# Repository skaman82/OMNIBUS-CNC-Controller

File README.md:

# OMNIBUS-CNC-Controller (WORK IN PROGRESS)
CNC Control Project (GRBL and ESTLCAM based). Please dont' sell the boards published here without my consent.

## OMNIBUS ESTLCAM Controller</br>
### FINISHED
</br>
• 8 inputs for sensors and buttons (IN6 is usable if you remoove the LED "L" from the Nano)</br>
• All inputs are isolated with optocouplers</br>
• Inputs 1-3 have selectable voltage (5/12v) so you can connect inductive proximity sensors directly</br>
• VFD outputs (Spindle ON/OFF and RPM control)</br>
• 5V PWM output</br>
• 3 Outputs for relays - the outputs have selectable voltage (5/12v) - OUT3 is automatically enabled on spindle ON</br>
• Feed/Speed override connectors (JST XH 3P)</br>
• Header for bluetooth serial module (HC-05)</br>
• Screw-Terminals for easy connection</br>
• Connector for the DRV-Shield</br>
</br>
## OMNIBUS GRBL 1.1 Controller - also ESTLCAM compatible</br>
### FINISHED
</br>
• Limit-Inputs XYZ have selectable voltage (5/12v) so you can connect inductive proximity sensors directly</br>
• ABORT/HOLD/RESUME/PROBE inputs</br>
• All inputs are isolated with optocouplers</br>
• VFD outputs (Spindle ON/OFF and RPM control)</br>
• 5V PWM Output</br>
• 2 Outputs for relay (SPINDLE_RELAIS / COOLANT) - the outputs have selectable voltage (5/12v) - SPINDLE RELAY is automatically enabled on spindle ON</br>
• Header for bluetooth serial module (HC-05)</br>
• Header for offline controller</br>
• Screw-Terminals for easy connection</br>
• Connector for the DRV-Shield</br>

NOTE: To use the "SPINDLE RELAY" and "VFD RUN" Outputs, please uncomment "define USE_SPINDLE_DIR_AS_ENABLE_PIN" in the GRBL config.h file.
</br>
## OMNIBUS DRV SHIELD (mounts on top the controll PCB with spacers)</br>
### Experimental stage
</br>
• Up to 10A current support (2oz copper PCB required)</br>
• 3-Axis stepper driver support (DRV8825/S109/TMC2100) with stepping config jumpers</br>
• Header for laser module (3p)</br>
• Laser module safety switch - PWM controlled</br>
• Header for an extra 12V 2A BEC to power a laser module (20w max)</br>
• 12V fan header</br>
• 12V Power supply for the OMNIBUS controller (so you don't need an extra 12v PSU for the controll board)</br>
• Screw-Terminals for easy connection</br>

NOTE: If powerting the OMNIBUS Controller with the DRV Shield, use a heatsink on the 12V LDO and provide good airflow - the LDO is getting hot and will
shut down if thermal protection kicks in.

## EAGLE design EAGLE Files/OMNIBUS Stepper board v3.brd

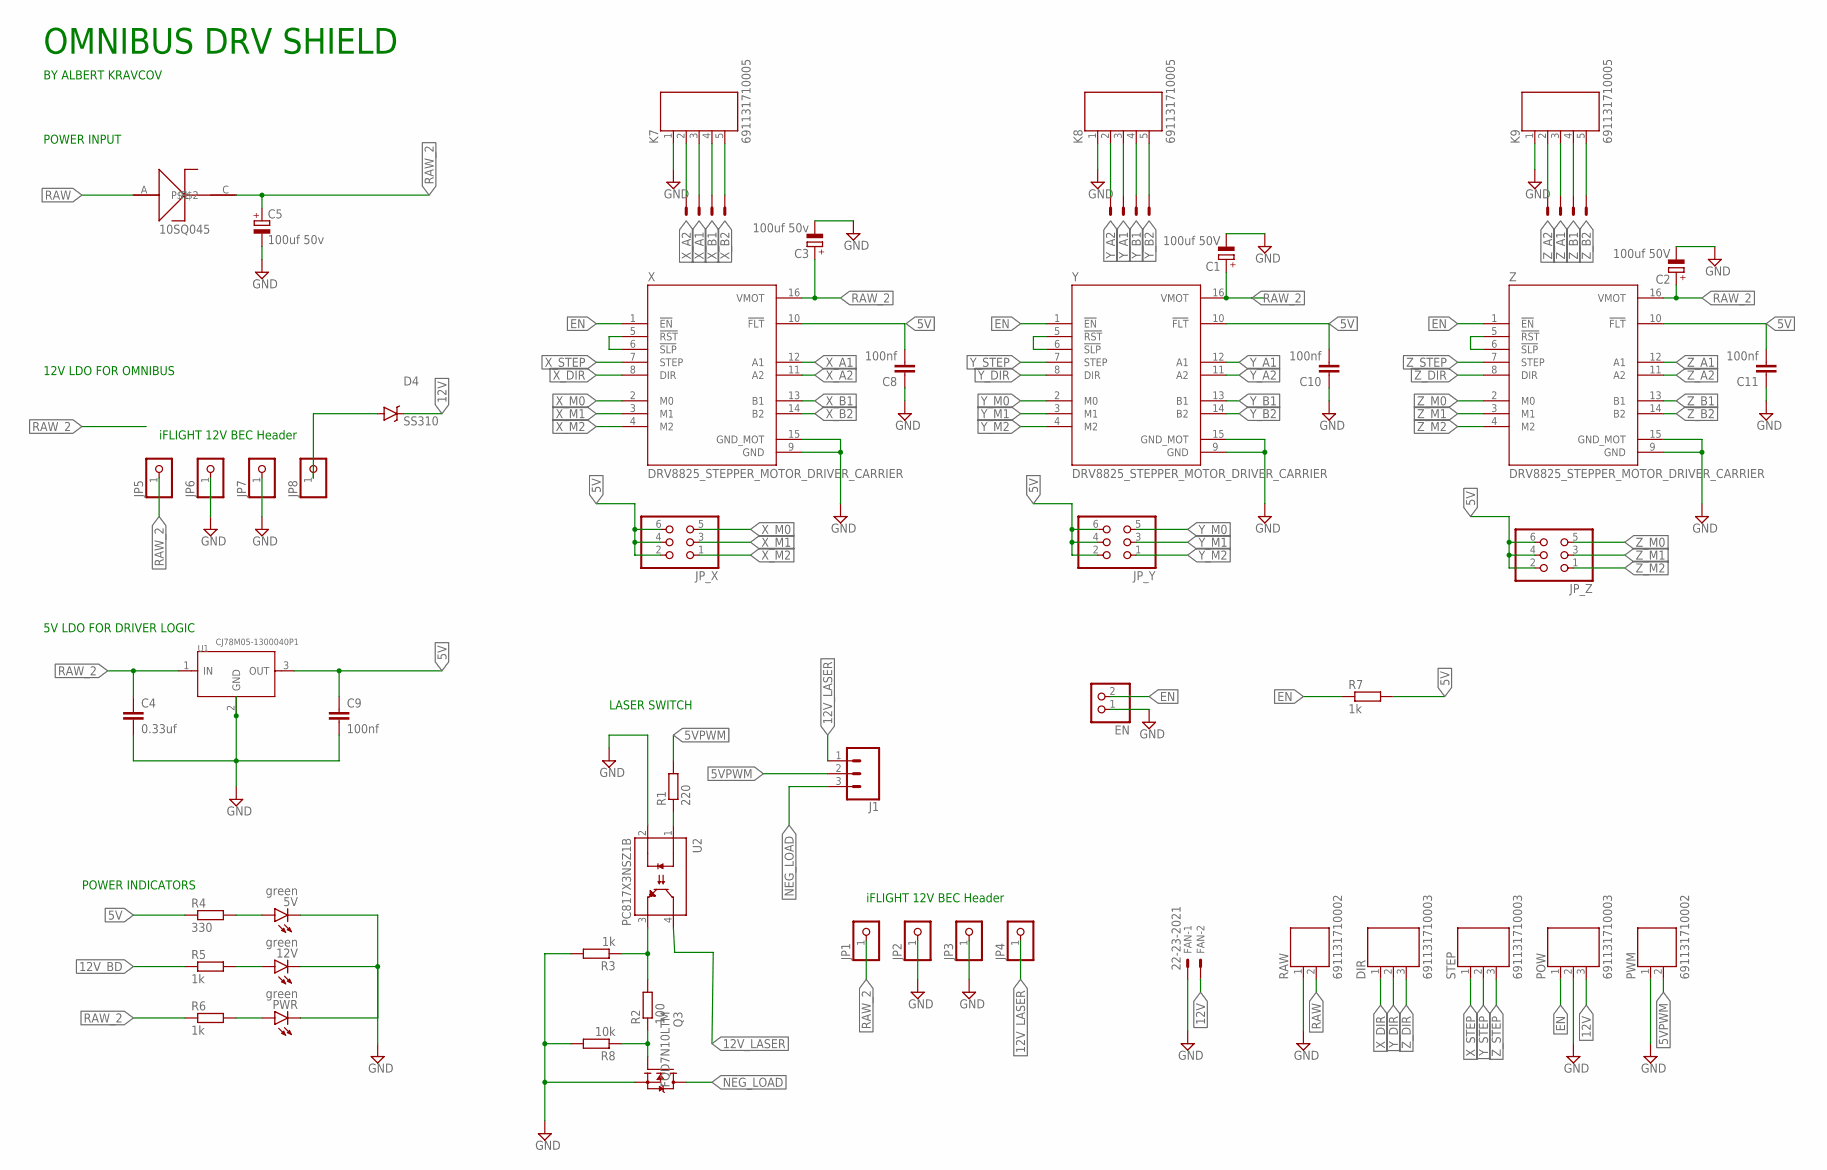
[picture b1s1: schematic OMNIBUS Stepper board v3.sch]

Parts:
5V, 12V: green; CHIPLED_0805
C1, C2: 100uf 50V; E5-6
C3: 100uf 50v; E5-6
C4: 0.33uf; C1206
C5: 100uf 50v; E5-8,5
C8, C10, C11: 100nf; C0805
C9: 100nf; C1206
D1: 10SQ045; DIOAD885W125L910D885
D4: SS310; DO-214AC
DIR: 691131710003
EN: PINHD-1X2; 1X02
FAN: 22-23-2021
J1: CONN_03; 1X03
JP1, JP2, JP3, JP4, JP5, JP6, JP7, JP8: PINHD-1X1; 1X01
JP_X: PINHD-2X3; 2X03
JP_Y: PINHD-2X3; 2X03
JP_Z: PINHD-2X3; 2X03
K7, K8, K9: 691131710005
POW: 691131710003
PWM: 691131710002
PWR: green; CHIPLED_0805
Q3: FQD7N10LTM; TO-252
R1: 220; R0805
R2: 100; R0805
R3, R5, R7: 1k; R0805
R4: 330; R0805
R6: 1k; R1206
R8: 10k; R0805
RAW: 691131710002
STEP: 691131710003
U1: CJ78M05-1300040P1; TO252
U2: PC817X3NSZ1B; DIP762W50P254L495H455Q4
X: DRV8825_STEPPER_MOTOR_DRIVER_CARRIER; IC_DRV8825_STEPPER_MOTOR_DRIVER_CARRIER
X_MOTOR: 22-23-2041
Y: DRV8825_STEPPER_MOTOR_DRIVER_CARRIER; IC_DRV8825_STEPPER_MOTOR_DRIVER_CARRIER
Y_MOTOR: 22-23-2041
Z: DRV8825_STEPPER_MOTOR_DRIVER_CARRIER; IC_DRV8825_STEPPER_MOTOR_DRIVER_CARRIER
Z_MOTOR: 22-23-2041

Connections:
5V: C8.2, C9.1, C10.2, C11.2, JP_X.2, JP_X.4, JP_X.6, JP_Y.2, JP_Y.4, JP_Y.6, JP_Z.2, JP_Z.4, JP_Z.6, R4.1, R7.2, U1.3 (OUT), X.10 (!FLT), Y.10 (!FLT), Z.10 (!FLT)
5VPWM: J1.2, PWM.2, R1.2
12V: D4.C, FAN.2, POW.3
12V_BD: D4.A, JP8.1, R5.1
12V_LASER: J1.1, JP4.1, U2.4 (COLLECTOR)
EN: EN.2, POW.1, R7.1, X.1 (!EN), Y.1 (!EN), Z.1 (!EN)
GND: 5V.C, 12V.C, C1.-, C2.-, C3.-, C4.2, C5.-, C8.1, C9.2, C10.1, C11.1, EN.1, FAN.1, JP2.1, JP3.1, JP6.1, JP7.1, K7.1, K8.1, K9.1, POW.2, PWM.1, PWR.C, Q3.3 (S), R3.2, R8.2, RAW.1, U1.2 (GND), U2.2 (CATHODE), X.9 (GND), X.15 (GND_MOT), Y.9 (GND), Y.15 (GND_MOT), Z.9 (GND), Z.15 (GND_MOT)
unnamed: Q3.1 (G), R2.1, R8.1
unnamed: 5V.A, R4.2
unnamed: R1.1, U2.1 (ANODE)
unnamed: R2.2, R3.1, U2.3 (EMITTER)
unnamed: 12V.A, R5.2
unnamed: PWR.A, R6.2
NC: Z.5 (!RST), Z.6 (!SLP)
NC2: Y.5 (!RST), Y.6 (!SLP)
NC3: X.5 (!RST), X.6 (!SLP)
NEG_LOAD: J1.3, Q3.T (D)
RAW: D1.A, RAW.2
RAW_2: C1.+, C2.+, C3.+, C4.1, C5.+, D1.C, JP1.1, JP5.1, R6.1, U1.1 (IN), X.16 (VMOT), Y.16 (VMOT), Z.16 (VMOT)
X_A1: K7.3, X.12 (A1), X_MOTOR.3
X_A2: K7.2, X.11 (A2), X_MOTOR.4
X_B1: K7.4, X.13 (B1), X_MOTOR.2
X_B2: K7.5, X.14 (B2), X_MOTOR.1
X_DIR: DIR.1, X.8 (DIR)
X_M0: JP_X.5, X.2 (M0)
X_M1: JP_X.3, X.3 (M1)
X_M2: JP_X.1, X.4 (M2)
X_STEP: STEP.1, X.7 (STEP)
Y_A1: K8.3, Y.12 (A1), Y_MOTOR.3
Y_A2: K8.2, Y.11 (A2), Y_MOTOR.4
Y_B1: K8.4, Y.13 (B1), Y_MOTOR.2
Y_B2: K8.5, Y.14 (B2), Y_MOTOR.1
Y_DIR: DIR.2, Y.8 (DIR)
Y_M0: JP_Y.5, Y.2 (M0)
Y_M1: JP_Y.3, Y.3 (M1)
Y_M2: JP_Y.1, Y.4 (M2)
Y_STEP: STEP.2, Y.7 (STEP)
Z_A1: K9.3, Z.12 (A1), Z_MOTOR.3
Z_A2: K9.2, Z.11 (A2), Z_MOTOR.4
Z_B1: K9.4, Z.13 (B1), Z_MOTOR.2
Z_B2: K9.5, Z.14 (B2), Z_MOTOR.1
Z_DIR: DIR.3, Z.8 (DIR)
Z_M0: JP_Z.5, Z.2 (M0)
Z_M1: JP_Z.3, Z.3 (M1)
Z_M2: JP_Z.1, Z.4 (M2)
Z_STEP: STEP.3, Z.7 (STEP)

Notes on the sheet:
LASER SWITCH
POWER INPUT
5V LDO FOR DRIVER LOGIC
12V LDO FOR OMNIBUS
POWER INDICATORS
iFLIGHT 12V BEC Header
OMNIBUS DRV SHIELD
BY ALBERT KRAVCOV
10SQ045

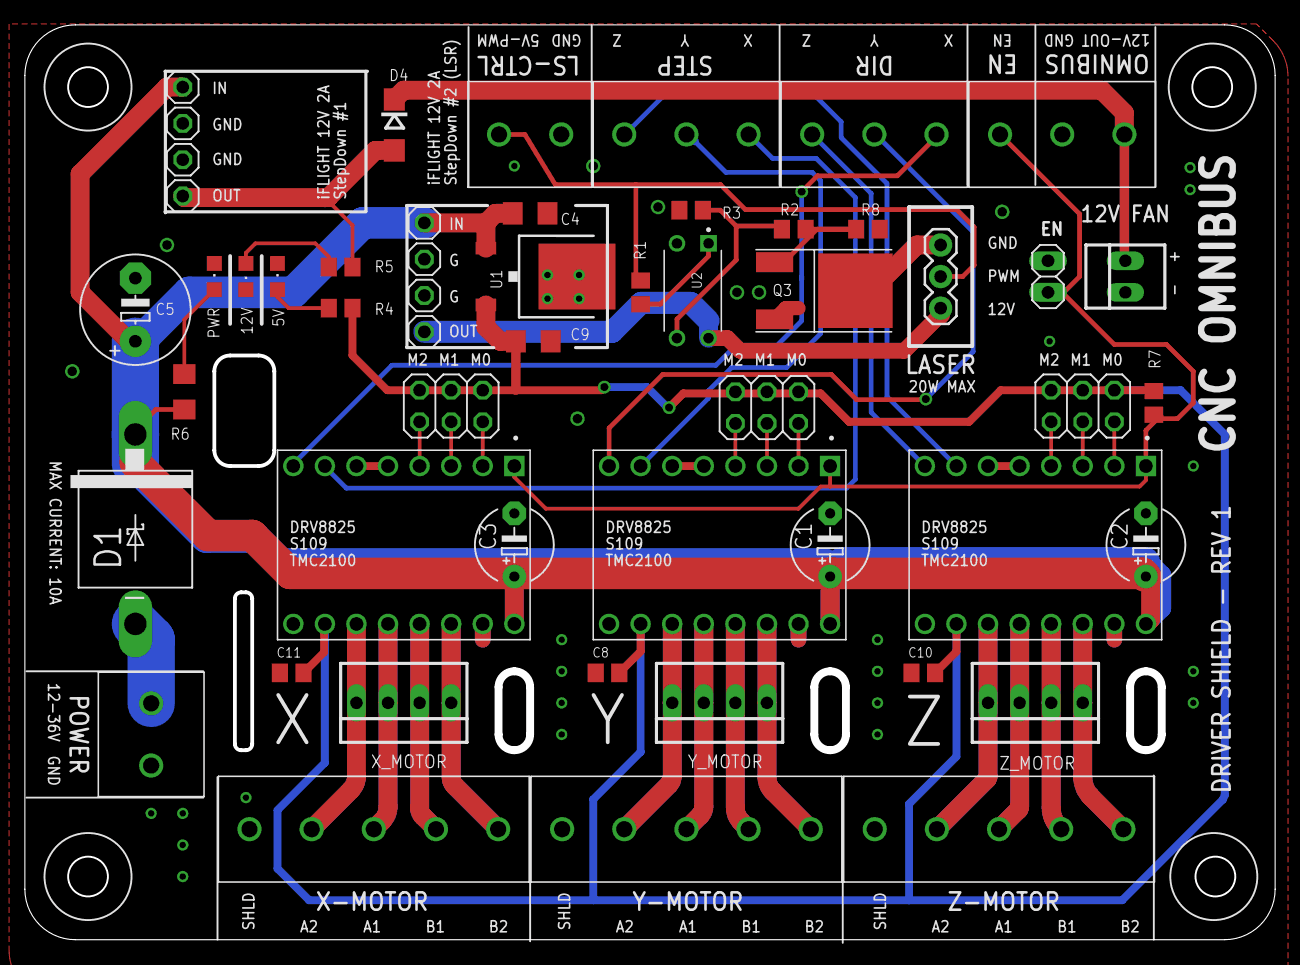
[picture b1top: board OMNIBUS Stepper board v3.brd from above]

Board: 2 copper layers, 99.9 x 72.9 mm, 53 parts (0 on the bottom side), 46 nets.

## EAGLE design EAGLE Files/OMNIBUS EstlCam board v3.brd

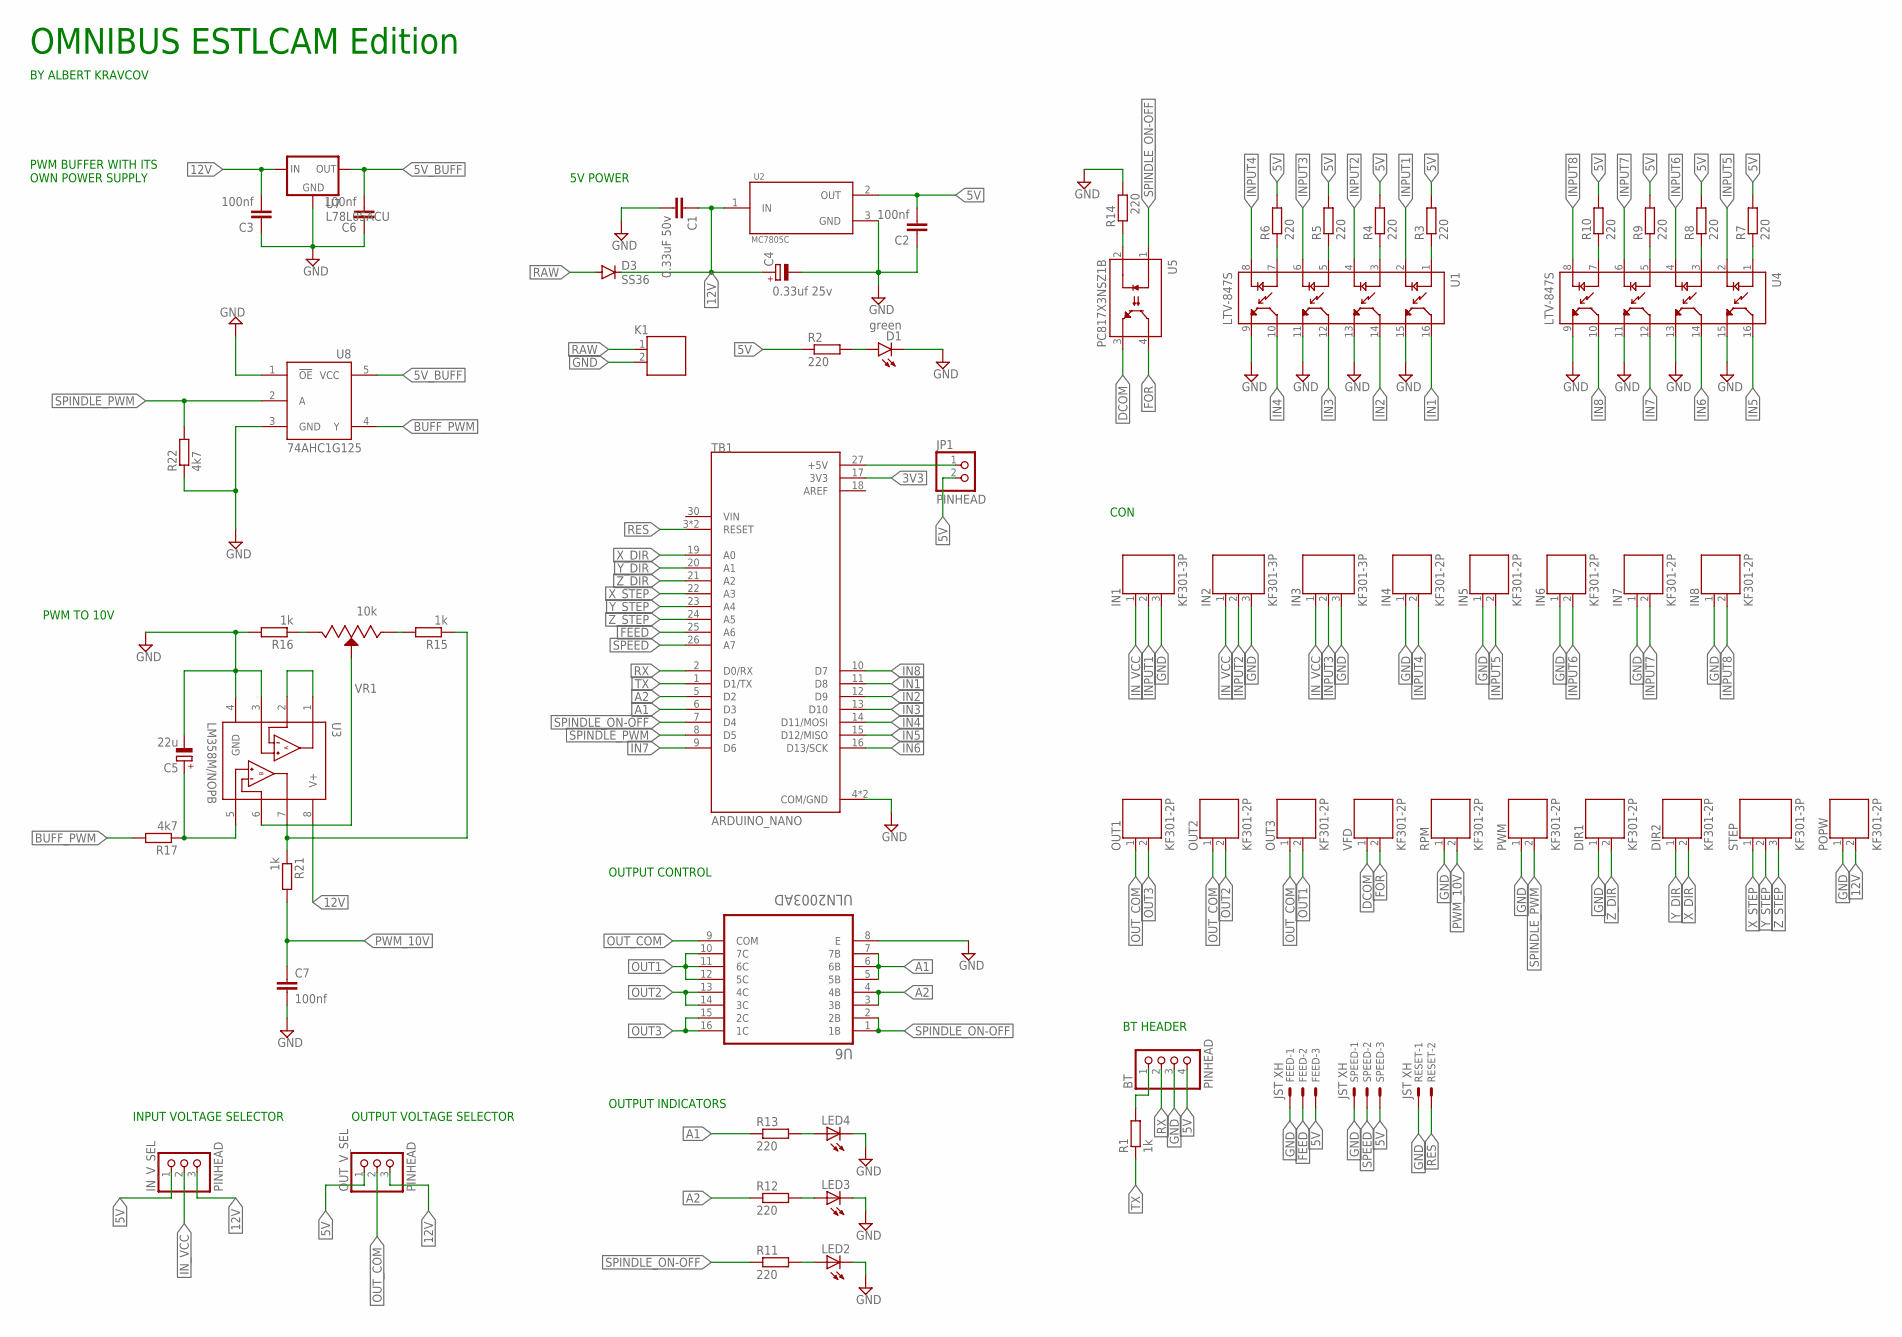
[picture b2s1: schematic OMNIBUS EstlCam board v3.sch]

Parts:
BT: PINHEAD; 1X04
C1: 0.33uF 50v; C1206
C2, C3, C6, C7: 100nf; C0805
C4: 0.33uf 25v; E2-5
C5: 22u; E2-5
D1: green; CHIPLED_0805
D3: SS36; SMB
DIR1, DIR2: KF301-2P; 691131710002
FEED: JST XH; 22-23-2031
IN1, IN2, IN3: KF301-3P; 691131710003
IN4, IN5, IN6, IN7, IN8: KF301-2P; 691131710002
IN_V_SEL: PINHEAD; 1X03
JP1: PINHEAD; 1X02
K1: 691131710002
LED2, LED3, LED4: LED_ESML0603; LED_SML0603
OUT1, OUT2, OUT3: KF301-2P; 691131710002
OUT_V_SEL: PINHEAD; 1X03
POPW: KF301-2P; 691131710002
PWM: KF301-2P; 691131710002
R1, R15, R16, R21: 1k; R0805
R2, R3, R4, R5, R6, R7, R8, R9, R10, R14: 220; R0805
R11, R12, R13: 220; R0603
R17: 4k7; R0603
R22: 4k7; R0805
RESET: JST XH; 22-23-2021
RPM: KF301-2P; 691131710002
SPEED: JST XH; 22-23-2031
STEP: KF301-3P; 691131710003
TB1: ARDUINO_NANO; SHIELD_ARDUINO_NANO
U1, U4: LTV-847S; SOIC254P1016X460-16N
U2: MC7805C; TO254P1515X470-3N
U3: LM358M/NOPB; SOIC127P599X175-8N
U5: PC817X3NSZ1B; DIP762W50P254L495H455Q4
U6: ULN2003AD; SOIC127P600X175-16N
U7: L78L05ACU; SOT89
U8: 74AHC1G125; SOT23-5L
VFD: KF301-2P; 691131710002
VR1: 10k; TRIM_3296W-1-502

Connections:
3V3: TB1.17 (3V3)
5V: BT.4, C2.2, FEED.3, IN_V_SEL.1, JP1.2, OUT_V_SEL.1, R2.1, R3.2, R4.2, R5.2, R6.2, R7.2, R8.2, R9.2, R10.2, SPEED.3, U2.2 (OUT)
5V_BUFF: C6.2, U7.1 (OUT), U8.5 (VCC)
12V: C1.1, C3.2, C4.+, D3.C, IN_V_SEL.3, OUT_V_SEL.3, POPW.2, U2.1 (IN), U3.8 (V+), U7.3 (IN)
A1: R13.1, TB1.6 (D3), U6.5 (5B), U6.6 (6B), U6.7 (7B)
A2: R12.1, TB1.5 (D2), U6.3 (3B), U6.4 (4B)
ARDU5V: JP1.1, TB1.27 (+5V)
AREF: TB1.18 (AREF)
BUFF_PWM: R17.2, U8.4 (Y)
D: R15.1, R21.1, U3.7 (OUTB)
DCOM: U5.3 (EMITTER), VFD.1
FEED: FEED.2, TB1.25 (A6)
FOR: U5.4 (COLLECTOR), VFD.2
GND: BT.3, C1.2, C2.1, C3.1, C4.-, C5.-, C6.1, C7.2, D1.C, DIR1.1, FEED.1, IN1.3, IN2.3, IN3.3, IN4.1, IN5.1, IN6.1, IN7.1, IN8.1, K1.2, LED2.C, LED3.C, LED4.C, POPW.1, PWM.1, R14.2, R16.2, R22.1, RESET.1, RPM.1, SPEED.1, TB1.4 (COM/GND), TB1.29 (COM/GND), U1.9 (ET3), U1.11 (ET2), U1.13 (ET1), U1.15 (ET), U2.3 (GND), U3.3 (+INA), U3.4 (GND), U4.9 (ET3), U4.11 (ET2), U4.13 (ET1), U4.15 (ET), U6.8 (E), U7.2 (GND), U8.1 (!OE), U8.3 (GND)
IN1: TB1.11 (D8), U1.16 (CT)
IN2: TB1.12 (D9), U1.14 (CT1)
IN3: TB1.13 (D10), U1.12 (CT2)
IN4: TB1.14 (D11/MOSI), U1.10 (CT3)
IN5: TB1.15 (D12/MISO), U4.16 (CT)
IN6: TB1.16 (D13/SCK), U4.14 (CT1)
IN7: TB1.9 (D6), U4.12 (CT2)
IN8: TB1.10 (D7), U4.10 (CT3)
INPUT1: IN1.2, U1.2 (C)
INPUT2: IN2.2, U1.4 (C1)
INPUT3: IN3.2, U1.6 (C2)
INPUT4: IN4.2, U1.8 (C3)
INPUT5: IN5.2, U4.2 (C)
INPUT6: IN6.2, U4.4 (C1)
INPUT7: IN7.2, U4.6 (C2)
INPUT8: IN8.2, U4.8 (C3)
IN_VCC: IN1.1, IN2.1, IN3.1, IN_V_SEL.2
unnamed: D1.A, R2.2
unnamed: R4.1, U1.3 (A1)
unnamed: R5.1, U1.5 (A2)
unnamed: R6.1, U1.7 (A3)
unnamed: R3.1, U1.1 (A)
unnamed: R7.1, U4.1 (A)
unnamed: R8.1, U4.3 (A1)
unnamed: R9.1, U4.5 (A2)
unnamed: R10.1, U4.7 (A3)
unnamed: LED3.A, R12.2
unnamed: LED2.A, R11.2
unnamed: LED4.A, R13.2
unnamed: R14.1, U5.2 (CATHODE)
unnamed: U3.6 (-INB), VR1.2 (WIPER)
unnamed: R15.2, VR1.1 (CCW)
unnamed: R16.1, VR1.3 (CW)
unnamed: C5.+, R17.1, U3.5 (+INB)
unnamed: U3.1 (OUTA), U3.2 (-INA)
unnamed: BT.1, R1.2
OUT1: OUT3.2, U6.10 (7C), U6.11 (6C), U6.12 (5C)
OUT2: OUT2.2, U6.13 (4C), U6.14 (3C)
OUT3: OUT1.2, U6.15 (2C), U6.16 (1C)
OUT_COM: OUT1.1, OUT2.1, OUT3.1, OUT_V_SEL.2, U6.9 (COM)
PWM_10V: C7.1, R21.2, RPM.2
RAW: D3.A, K1.1
RES: RESET.2, TB1.3 (RESET), TB1.28 (RESET)
RX: BT.2, TB1.2 (D0/RX)
SPEED: SPEED.2, TB1.26 (A7)
SPINDLE_ON-OFF: R11.1, TB1.7 (D4), U5.1 (ANODE), U6.1 (1B), U6.2 (2B)
SPINDLE_PWM: PWM.2, R22.2, TB1.8 (D5), U8.2 (A)
TX: R1.1, TB1.1 (D1/TX)
X_DIR: DIR2.2, TB1.19 (A0)
X_STEP: STEP.1, TB1.22 (A3)
Y_DIR: DIR2.1, TB1.20 (A1)
Y_STEP: STEP.2, TB1.23 (A4)
Z_DIR: DIR1.2, TB1.21 (A2)
Z_STEP: STEP.3, TB1.24 (A5)

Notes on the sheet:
PWM BUFFER WITH ITS OWN POWER SUPPLY
OUTPUT VOLTAGE SELECTOR
PWM TO 10V
INPUT VOLTAGE SELECTOR
OUTPUT INDICATORS
OUTPUT CONTROL
CON
5V POWER
BT HEADER
OMNIBUS ESTLCAM Edition
BY ALBERT KRAVCOV

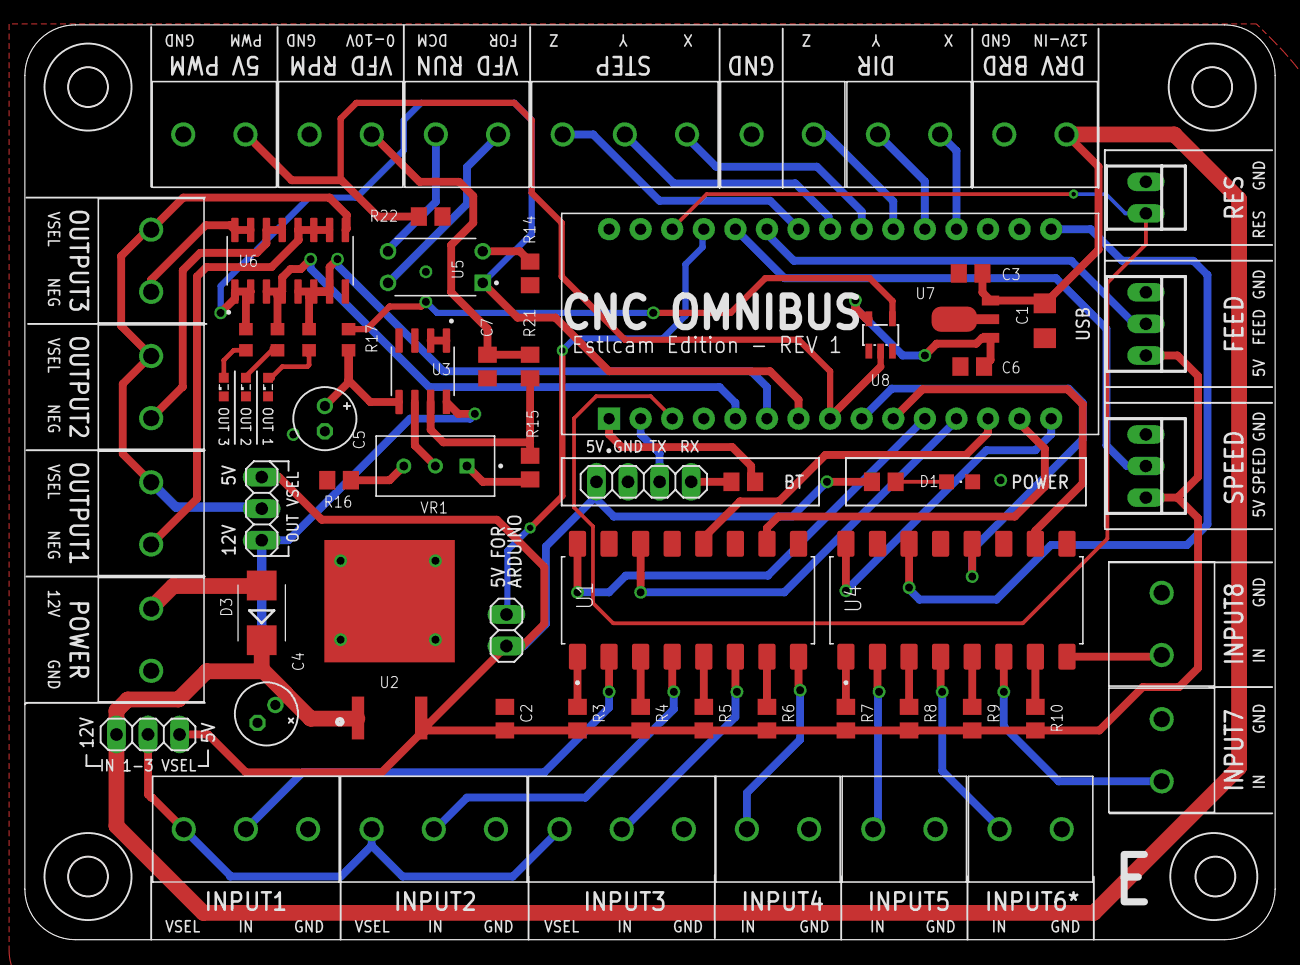
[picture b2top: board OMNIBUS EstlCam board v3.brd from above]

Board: 2 copper layers, 100.4 x 73.4 mm, 67 parts (0 on the bottom side), 66 nets.

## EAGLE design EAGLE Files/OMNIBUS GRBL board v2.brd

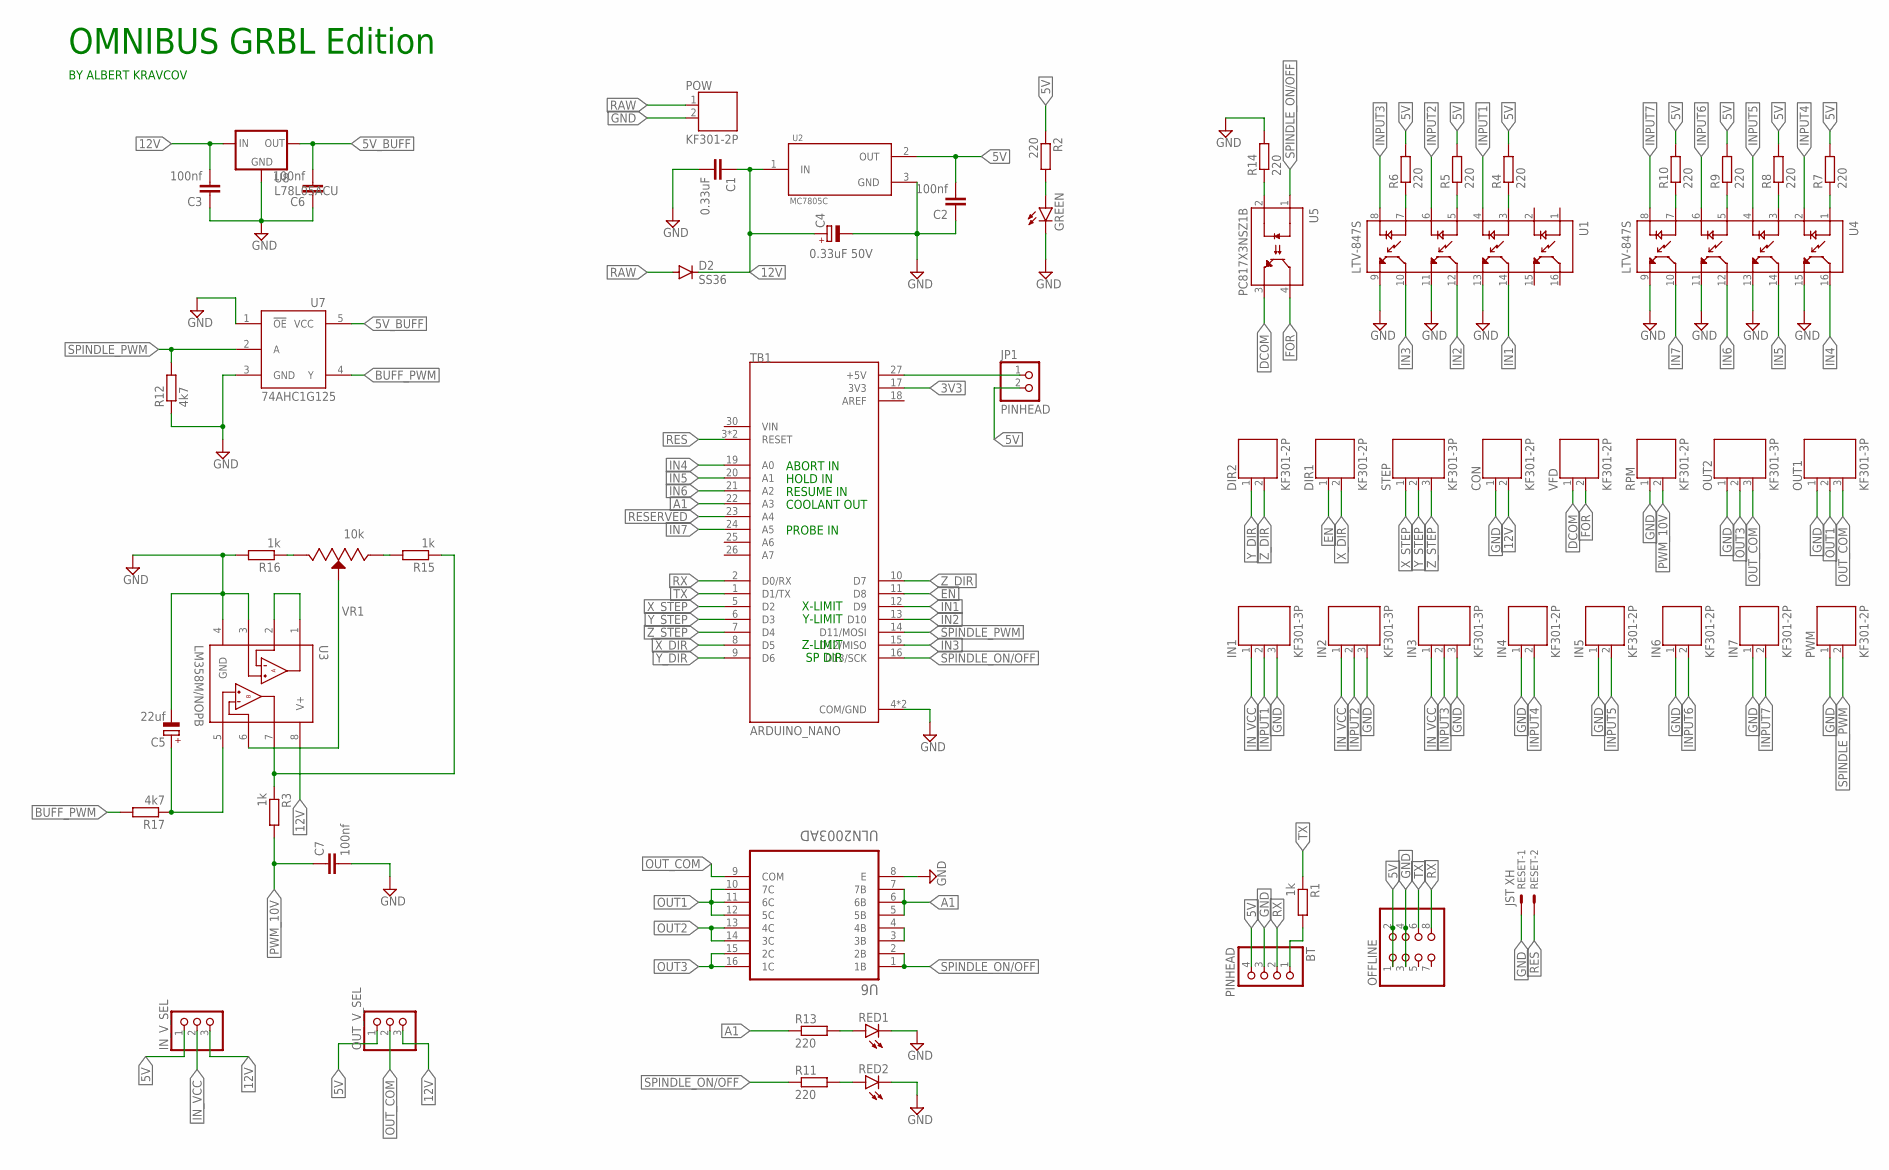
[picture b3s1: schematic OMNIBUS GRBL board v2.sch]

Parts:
BT: PINHEAD; 1X04
C1: 0.33uF; C1206K
C2: 100nf; C0805K
C3, C6, C7: 100nf; C0805
C4: 0.33uF 50V; E2-5
C5: 22uf; E2-5
CON: KF301-2P; 691131710002
D2: SS36; SMB
DIR1, DIR2: KF301-2P; 691131710002
GREEN: LEDCHIPLED_0805; CHIPLED_0805
IN1, IN2, IN3: KF301-3P; 691131710003
IN4, IN5, IN6, IN7: KF301-2P; 691131710002
IN_V_SEL: PINHD-1X3; 1X03
JP1: PINHEAD; 1X02
OFFLINE: PINHD-2X4; 2X04
OUT1, OUT2: KF301-3P; 691131710003
OUT_V_SEL: PINHD-1X3; 1X03
POW: KF301-2P; 691131710002
PWM: KF301-2P; 691131710002
R1, R3, R15, R16: 1k; R0805
R2, R11, R13: 220; R0603
R4, R5, R6, R7, R8, R9, R10, R14: 220; R0805
R12, R17: 4k7; R0805
RED1, RED2: LEDCHIPLED_0805; CHIPLED_0805
RESET: JST XH; 22-23-2021
RPM: KF301-2P; 691131710002
STEP: KF301-3P; 691131710003
TB1: ARDUINO_NANO; SHIELD_ARDUINO_NANO
U1, U4: LTV-847S; SOIC254P1016X460-16N
U2: MC7805C; TO254P1515X470-3N
U3: LM358M/NOPB; SOIC127P599X175-8N
U5: PC817X3NSZ1B; DIP762W50P254L495H455Q4
U6: ULN2003AD; SOIC127P600X175-16N
U7: 74AHC1G125; SOT23-5L
U8: L78L05ACU; SOT89
VFD: KF301-2P; 691131710002
VR1: 10k; TRIM_3296W-1-502

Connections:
3V3: TB1.17 (3V3)
5V: BT.4, C2.2, IN_V_SEL.1, JP1.2, OFFLINE.1, OFFLINE.2, OUT_V_SEL.1, R2.1, R4.2, R5.2, R6.2, R7.2, R8.2, R9.2, R10.2, U2.2 (OUT)
5V_BUFF: C6.2, U7.5 (VCC), U8.1 (OUT)
12V: C1.1, C3.2, C4.+, CON.2, D2.C, IN_V_SEL.3, OUT_V_SEL.3, U2.1 (IN), U3.8 (V+), U8.3 (IN)
A1: R13.1, TB1.22 (A3), U6.5 (5B), U6.6 (6B), U6.7 (7B)
A2: U6.3 (3B), U6.4 (4B)
ARDUPWR: JP1.1, TB1.27 (+5V)
AREF: TB1.18 (AREF)
BUFF_PWM: R17.2, U7.4 (Y)
DCOM: U5.3 (EMITTER), VFD.1
EN: DIR1.1, TB1.11 (D8)
FOR: U5.4 (COLLECTOR), VFD.2
GND: BT.3, C1.2, C2.1, C3.1, C4.-, C5.-, C6.1, C7.2, CON.1, GREEN.C, IN1.3, IN2.3, IN3.3, IN4.1, IN5.1, IN6.1, IN7.1, OFFLINE.3, OFFLINE.4, OUT1.1, OUT2.1, POW.2, PWM.1, R12.1, R14.2, R16.2, RED1.C, RED2.C, RESET.1, RPM.1, TB1.4 (COM/GND), TB1.29 (COM/GND), U1.9 (ET3), U1.11 (ET2), U1.13 (ET1), U2.3 (GND), U3.3 (+INA), U3.4 (GND), U4.9 (ET3), U4.11 (ET2), U4.13 (ET1), U4.15 (ET), U6.8 (E), U7.1 (!OE), U7.3 (GND), U8.2 (GND)
IN1: TB1.12 (D9), U1.14 (CT1)
IN2: TB1.13 (D10), U1.12 (CT2)
IN3: TB1.15 (D12/MISO), U1.10 (CT3)
IN4: TB1.19 (A0), U4.16 (CT)
IN5: TB1.20 (A1), U4.14 (CT1)
IN6: TB1.21 (A2), U4.12 (CT2)
IN7: TB1.24 (A5), U4.10 (CT3)
INPUT1: IN1.2, U1.4 (C1)
INPUT2: IN2.2, U1.6 (C2)
INPUT3: IN3.2, U1.8 (C3)
INPUT4: IN4.2, U4.2 (C)
INPUT5: IN5.2, U4.4 (C1)
INPUT6: IN6.2, U4.6 (C2)
INPUT7: IN7.2, U4.8 (C3)
IN_VCC: IN1.1, IN2.1, IN3.1, IN_V_SEL.2
unnamed: GREEN.A, R2.2
unnamed: R4.1, U1.3 (A1)
unnamed: R5.1, U1.5 (A2)
unnamed: R6.1, U1.7 (A3)
unnamed: R7.1, U4.1 (A)
unnamed: R8.1, U4.3 (A1)
unnamed: R9.1, U4.5 (A2)
unnamed: R10.1, U4.7 (A3)
unnamed: R11.2, RED2.A
unnamed: R13.2, RED1.A
unnamed: R14.1, U5.2 (CATHODE)
unnamed: U3.6 (-INB), VR1.2 (WIPER)
unnamed: R15.2, VR1.1 (CCW)
unnamed: R16.1, VR1.3 (CW)
unnamed: C5.+, R17.1, U3.5 (+INB)
unnamed: U3.1 (OUTA), U3.2 (-INA)
unnamed: BT.1, R1.2
OUT1: OUT1.2, U6.10 (7C), U6.11 (6C), U6.12 (5C)
OUT2: U6.13 (4C), U6.14 (3C)
OUT3: OUT2.2, U6.15 (2C), U6.16 (1C)
OUT_COM: OUT1.3, OUT2.3, OUT_V_SEL.2, U6.9 (COM)
PWM_10V: C7.1, R3.1, R3.2, R15.1, RPM.2, U3.7 (OUTB)
RAW: D2.A, POW.1
RES: RESET.2, TB1.3 (RESET), TB1.28 (RESET)
RESERVED: TB1.23 (A4)
RX: BT.2, OFFLINE.8, TB1.2 (D0/RX)
SPINDLE_ON/OFF: R11.1, TB1.16 (D13/SCK), U5.1 (ANODE), U6.1 (1B), U6.2 (2B)
SPINDLE_PWM: PWM.2, R12.2, TB1.14 (D11/MOSI), U7.2 (A)
TX: OFFLINE.6, R1.1, TB1.1 (D1/TX)
X_DIR: DIR1.2, TB1.8 (D5)
X_STEP: STEP.1, TB1.5 (D2)
Y_DIR: DIR2.1, TB1.9 (D6)
Y_STEP: STEP.2, TB1.6 (D3)
Z_DIR: DIR2.2, TB1.10 (D7)
Z_STEP: STEP.3, TB1.7 (D4)

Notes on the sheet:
SP DIR
ABORT IN
HOLD IN
RESUME IN
COOLANT OUT
PROBE IN
Z-LIMIT
Y-LIMIT
X-LIMIT
OMNIBUS GRBL Edition
BY ALBERT KRAVCOV

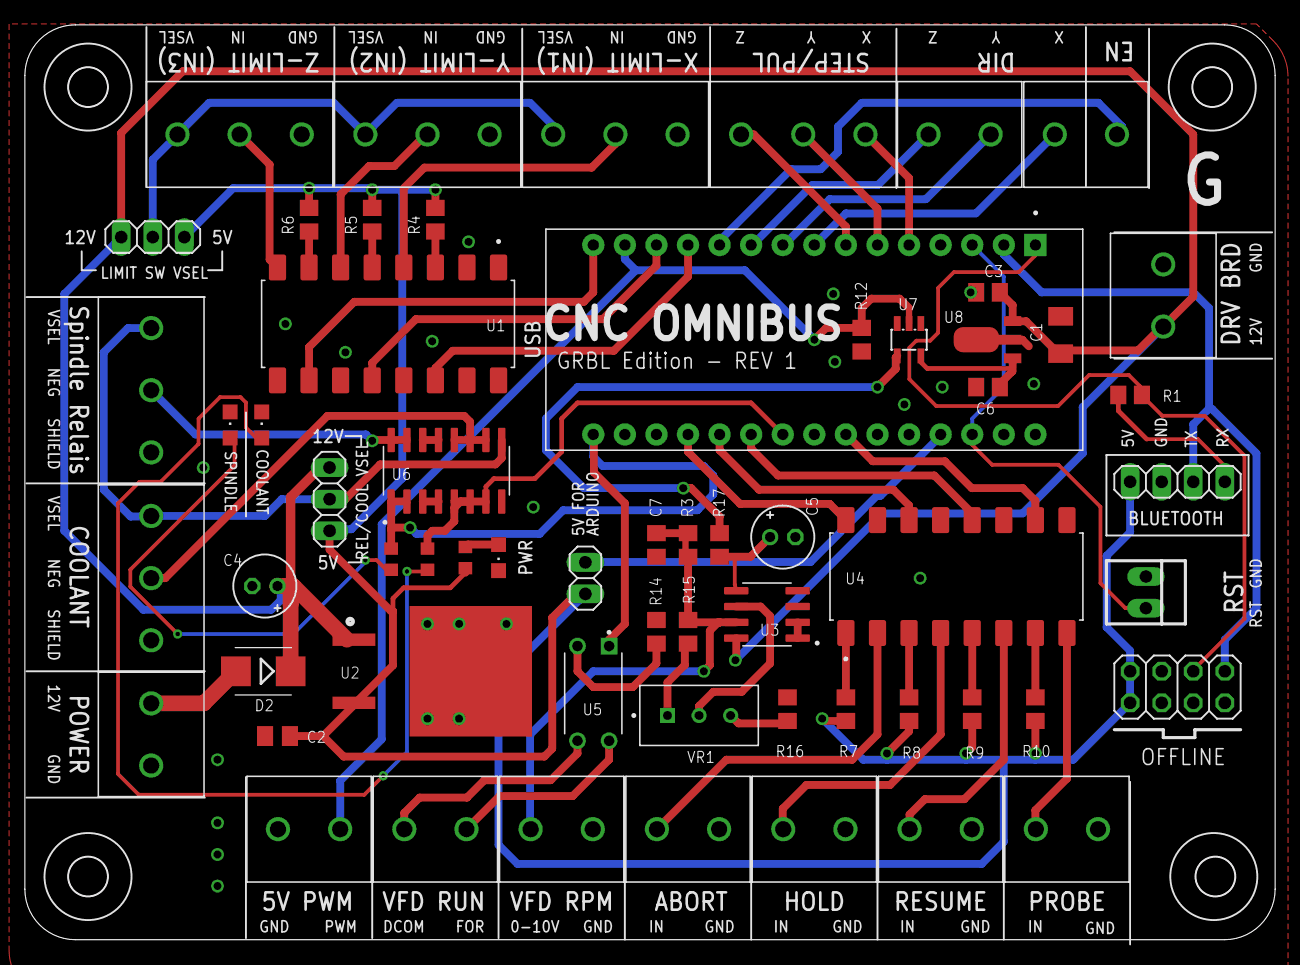
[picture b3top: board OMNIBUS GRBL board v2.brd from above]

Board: 2 copper layers, 100.4 x 73.4 mm, 61 parts (0 on the bottom side), 60 nets.

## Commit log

2021-05-05 Initial File Upload
2021-05-05 Reorder
2021-05-05 Renaming Files
2021-05-05 Extra files
2021-05-05 STL Upload
2021-05-05 label fix
2021-05-06 PCB Bugfixes and polishing
    • DRV Shield had an routing error (laser indicator LED) also R3 had a wrong value
    • New Footprint for the 0.33uF Caps
    • Silkscreen polishing
    • almost all LEDs are 0805 package now
2021-05-07 Changed voltage regulators
2021-05-17 clean up
    also added BOM
2021-05-27 new DRV board version and updates
2021-05-28 uninvert font

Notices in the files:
parts and their libraries:
Wurth_Terminal_Blocks_Connectors_rev15d: Copyright: Würth Elektronik
SparkFun-Connectors: Licensing: Creative Commons ShareAlike 4.0 International - https://creativecommons.org/licenses/by-sa/4.0
